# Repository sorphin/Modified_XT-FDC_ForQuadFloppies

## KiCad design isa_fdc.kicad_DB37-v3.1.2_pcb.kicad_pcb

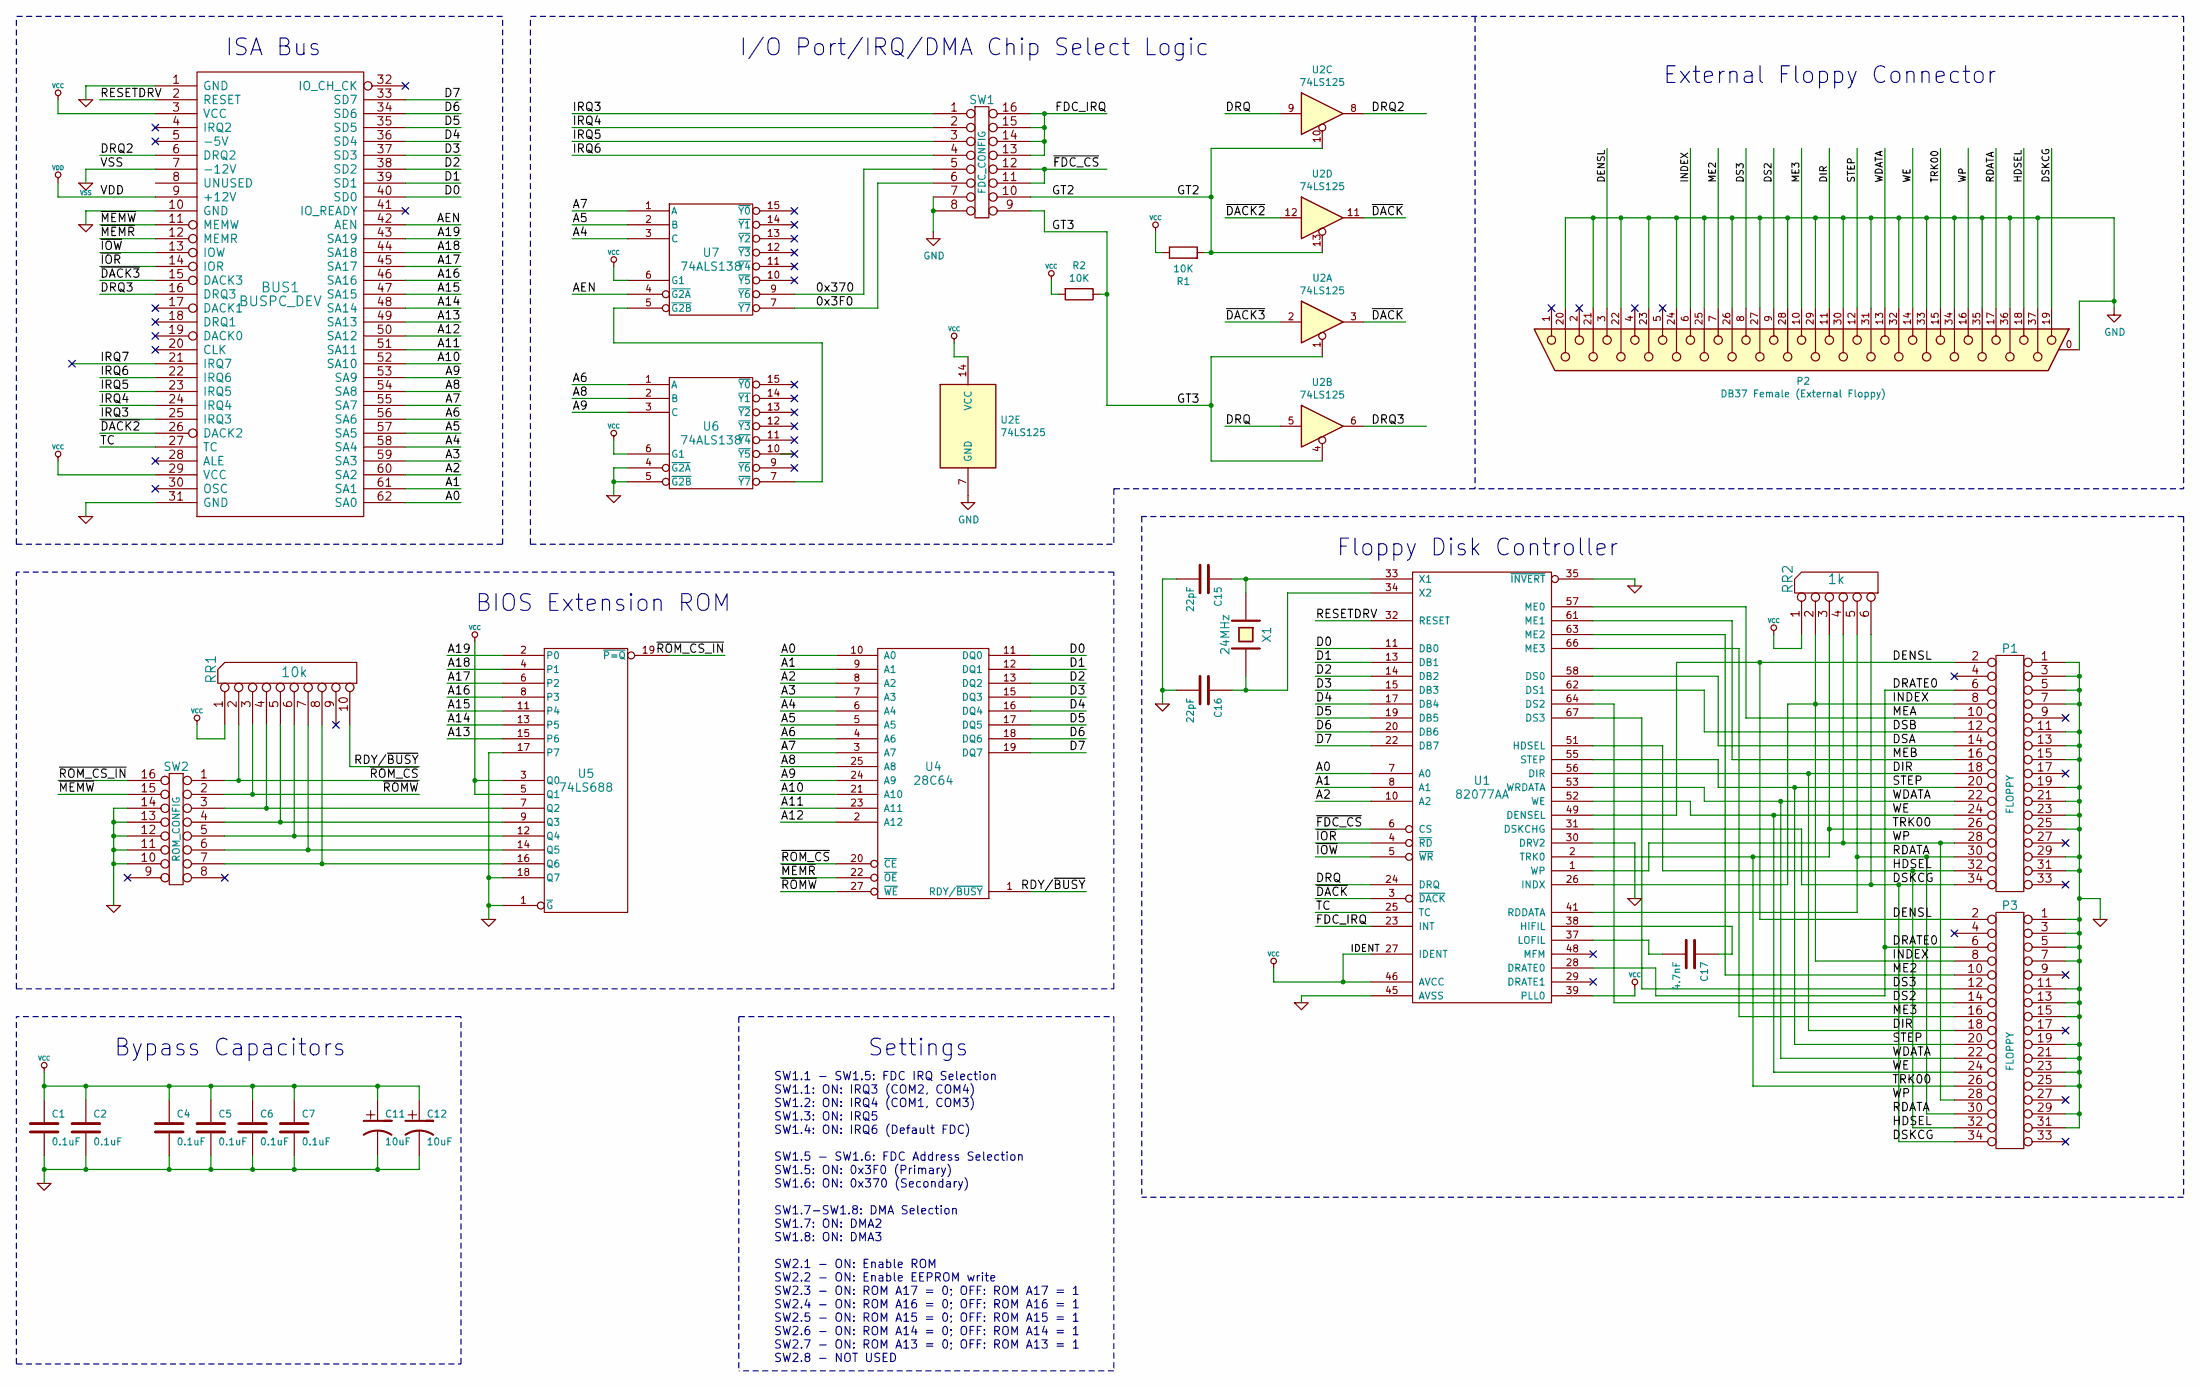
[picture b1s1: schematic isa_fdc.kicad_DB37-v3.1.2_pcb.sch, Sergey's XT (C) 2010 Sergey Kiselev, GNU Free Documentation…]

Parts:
BUS1: BUSPC_DEV
C1, C2, C4, C5, C6, C7: 0.1uF
C11, C12: 10uF
C15, C16: 22pF
C17: 4.7nF
P1, P3: FLOPPY
P2: DB37 Female (External Floppy)
R1, R2: 10K
RR1: 10k
RR2: 1k
SW1: FDC_CONFIG
SW2: ROM_CONFIG
U1: 82077AA
U2: 74LS125
U4: 28C64
U5: 74LS688
U6, U7: 74ALS138
X1: 24MHz

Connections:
/A0: BUS1.62 (SA0), U1.7 (A0), U4.10 (A0)
/A1: BUS1.61 (SA1), U1.8 (A1), U4.9 (A1)
/A2: BUS1.60 (SA2), U1.10 (A2), U4.8 (A2)
/A3: BUS1.59 (SA3), U4.7 (A3)
/A4: BUS1.58 (SA4), U4.6 (A4), U7.3 (C)
/A5: BUS1.57 (SA5), U4.5 (A5), U7.2 (B)
/A6: BUS1.56 (SA6), U4.4 (A6), U6.1 (A)
/A7: BUS1.55 (SA7), U4.3 (A7), U7.1 (A)
/A8: BUS1.54 (SA8), U4.25 (A8), U6.2 (B)
/A9: BUS1.53 (SA9), U4.24 (A9), U6.3 (C)
/A10: BUS1.52 (SA10), U4.21 (A10)
/A11: BUS1.51 (SA11), U4.23 (A11)
/A12: BUS1.50 (SA12), U4.2 (A12)
/A13: BUS1.49 (SA13), U5.15 (P6)
/A14: BUS1.48 (SA14), U5.13 (P5)
/A15: BUS1.47 (SA15), U5.11 (P4)
/A16: BUS1.46 (SA16), U5.8 (P3)
/A17: BUS1.45 (SA17), U5.6 (P2)
/A18: BUS1.44 (SA18), U5.4 (P1)
/A19: BUS1.43 (SA19), U5.2 (P0)
/AEN: BUS1.42 (AEN), U7.4 (~G2A)
/D0: BUS1.40 (SD0), U1.11 (DB0), U4.11 (DQ0)
/D1: BUS1.39 (SD1), U1.13 (DB1), U4.12 (DQ1)
/D2: BUS1.38 (SD2), U1.14 (DB2), U4.13 (DQ2)
/D3: BUS1.37 (SD3), U1.15 (DB3), U4.15 (DQ3)
/D4: BUS1.36 (SD4), U1.17 (DB4), U4.16 (DQ4)
/D5: BUS1.35 (SD5), U1.19 (DB5), U4.17 (DQ5)
/D6: BUS1.34 (SD6), U1.20 (DB6), U4.18 (DQ6)
/D7: BUS1.33 (SD7), U1.22 (DB7), U4.19 (DQ7)
/DENSL: P1.2, P2.3, P3.2, U1.49 (DENSEL)
/DIR: P1.18, P2.11, P3.18, U1.56 (DIR)
/DRATE0: P1.6, P3.6, U1.28 (DRATE0)
/DRQ: U1.24 (DRQ), U2.5, U2.9
/DRQ2: BUS1.6 (DRQ2), U2.8
/DRQ3: BUS1.16 (DRQ3), U2.6
/DS2: P2.9, P3.14, U1.64 (DS2)
/DS3: P2.8, P3.12, U1.67 (DS3)
/DSA: P1.14, U1.58 (DS0)
/DSB: P1.12, U1.62 (DS1)
/DSKCG: P1.34, P2.19, P3.34, RR2.6, U1.31 (DSKCHG)
/FDC_IRQ: SW1.13, SW1.14, SW1.15, SW1.16, U1.23 (INT)
/GT2: R1.2, SW1.10, U2.10, U2.13
/GT3: R2.1, SW1.9, U2.1, U2.4
/HDSEL: P1.32, P2.18, P3.32, U1.51 (HDSEL)
/INDEX: P1.8, P2.6, P3.8, RR2.2, U1.26 (INDX)
/IRQ3: BUS1.25 (IRQ3), SW1.1
/IRQ4: BUS1.24 (IRQ4), SW1.2
/IRQ5: BUS1.23 (IRQ5), SW1.3
/IRQ6: BUS1.22 (IRQ6), SW1.4
/IRQ7: BUS1.21 (IRQ7)
/ME2: P2.7, P3.10, U1.63 (ME2)
/ME3: P2.10, P3.16, U1.66 (ME3)
/MEA: P1.10, U1.57 (ME0)
/MEB: P1.16, U1.61 (ME1)
/RDATA: P1.30, P2.17, P3.30, RR2.5, U1.41 (RDDATA)
/RDY/~BUSY: RR1.10, U4.1 (RDY/~BUSY)
/RESETDRV: BUS1.2 (RESET), U1.32 (RESET)
/STEP: P1.20, P2.12, P3.20, U1.55 (STEP)
/TC: BUS1.27 (TC), U1.25 (TC)
/TRK00: P1.26, P2.15, P3.26, RR2.3, U1.2 (TRK0)
/WDATA: P1.22, P2.13, P3.22, U1.53 (WRDATA)
/WE: P1.24, P2.14, P3.24, U1.52 (WE)
/WP: P1.28, P2.16, P3.28, RR2.4, U1.1 (WP)
/~DACK: U1.3 (~DACK), U2.3, U2.11
/~DACK2: BUS1.26 (DACK2), U2.12
/~DACK3: BUS1.15 (DACK3), U2.2
/~FDC_CS: SW1.11, SW1.12, U1.6 (CS)
/~IOR: BUS1.14 (IOR), U1.4 (~RD)
/~IOW: BUS1.13 (IOW), U1.5 (~WR)
/~MEMR: BUS1.12 (MEMR), U4.22 (~OE)
/~MEMW: BUS1.11 (MEMW), SW2.15
/~ROMW: RR1.3, SW2.2, U4.27 (~WE)
/~ROM_CS: RR1.2, SW2.1, U4.20 (~CE)
/~ROM_CS_IN: SW2.16, U5.19 (~P=Q)
GND: BUS1.1 (GND), BUS1.10 (GND), BUS1.31 (GND), C1.2, C2.2, C4.2, C5.2, C6.2, C7.2, C11.2, C12.2, C15.2, C16.2, P1.1, P1.3, P1.5, P1.7, P1.11, P1.13, P1.15, P1.19, P1.21, P1.23, P1.25, P1.29, P1.31, P2.0 (PAD), P2.20, P2.21, P2.22, P2.23, P2.24, P2.25, P2.26, P2.27, P2.28, P2.29, P2.30, P2.31, P2.32, P2.33, P2.34, P2.35, P2.36, P2.37, P3.1, P3.3, P3.5, P3.7, P3.11, P3.13, P3.15, P3.19, P3.21, P3.23, P3.25, P3.29, P3.31, SW1.7, SW1.8, SW2.10, SW2.11, SW2.12, SW2.13, SW2.14, U1.9 (GND), U1.12 (GND), U1.16 (GND), U1.21 (GND), U1.30 (DRV2), U1.35 (~INVERT), U1.36 (GND), U1.45 (AVSS), U1.50 (GND), U1.54 (GND), U1.59 (GND), U1.65 (GND), U2.7 (GND), U4.14 (GND), U5.1 (~G), U5.10 (GND), U5.17 (P7), U5.18 (Q7), U6.4 (~G2A), U6.5 (~G2B), U6.8 (GND), U7.8 (GND)
unnamed: C15.1, U1.33 (X1), X1.1
unnamed: C16.1, U1.34 (X2), X1.2
unnamed: C17.1, U1.38 (HIFIL)
unnamed: C17.2, U1.37 (LOFIL)
unnamed: RR1.4, SW2.3, U5.7 (Q2)
unnamed: RR1.5, SW2.4, U5.9 (Q3)
unnamed: RR1.6, SW2.5, U5.12 (Q4)
unnamed: RR1.7, SW2.6, U5.14 (Q5)
unnamed: RR1.8, SW2.7, U5.16 (Q6)
unnamed: U6.7 (~Y7), U7.5 (~G2B)
VCC: BUS1.3 (VCC), BUS1.29 (VCC), C1.1, C2.1, C4.1, C5.1, C6.1, C7.1, C11.1, C12.1, R1.1, R2.2, RR1.1 (COM), RR2.1 (COM), U1.18 (VCC), U1.27 (IDENT), U1.39 (PLL0), U1.40 (VCC), U1.46 (AVCC), U1.60 (VCC), U1.68 (VCC), U2.14 (VCC), U4.28 (VCC), U5.3 (Q0), U5.5 (Q1), U5.20 (VCC), U6.6 (G1), U6.16 (VCC), U7.6 (G1), U7.16 (VCC)
VDD: BUS1.9 (+12V)
VSS: BUS1.7 (-12V)

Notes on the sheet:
ISA Bus
BIOS Extension ROM
Bypass Capacitors
I/O Port/IRQ/DMA Chip Select Logic
Floppy Disk Controller
Settings
SW1.1 - SW1.5: FDC IRQ Selection SW1.1: ON: IRQ3 (COM2, COM4) SW1.2: ON: IRQ4 (COM1, COM3) SW1.3: ON: IRQ5 SW1.4: ON: IRQ6 (Default FDC) SW1.5 - SW1.6: FDC Address Selection SW1.5: ON: 0x3F0 (Primary) SW1.6: ON: 0x370 (Secondary) SW1.7-SW1.8: DMA Selection SW1.7: ON: DMA2 SW1.8: ON: DMA3 SW2.1 - ON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
External Floppy Connector

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
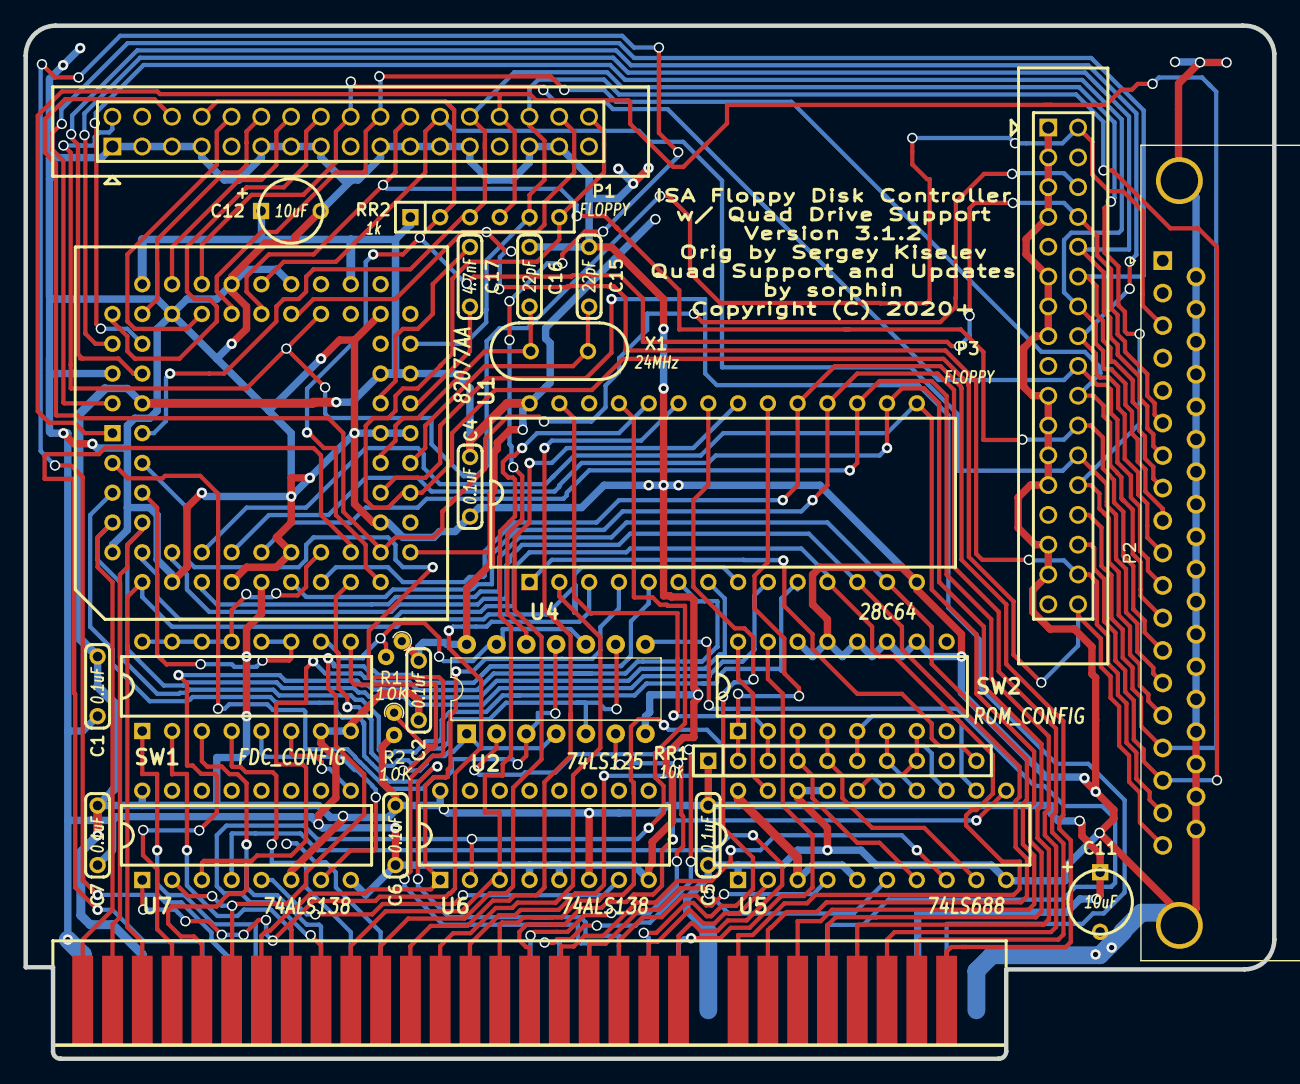
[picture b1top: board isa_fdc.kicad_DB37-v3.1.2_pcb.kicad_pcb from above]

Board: 2 copper layers, 106.5 x 88.1 mm, 28 parts (0 on the bottom side), 87 nets.

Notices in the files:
isa_fdc.kicad_DB37-v3.1.2_pcb.kicad_pcb:
Copyright (C) 2020+
isa_fdc.kicad_DB37-v3.1.2_pcb.sch:
Sergey's XT (C) 2010 Sergey Kiselev, GNU Free Documentation License (GFDL)
